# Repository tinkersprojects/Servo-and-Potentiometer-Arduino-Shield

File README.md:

# Servo-and-Potentiometer-Arduino-Shield
[https://tinkersprojects.com/](https://tinkersprojects.com/)

This shield is for the Arduino uno and has 6 potentiometer on every analog pin. The shield can also hold 14 servos (one for every digital pin). There are also 2 buttons on the inturuptet pins 2 and 3. 

Can get the PCB from https://www.tindie.com/products/williambailes/servo-and-potentiometer-arduino-shield/

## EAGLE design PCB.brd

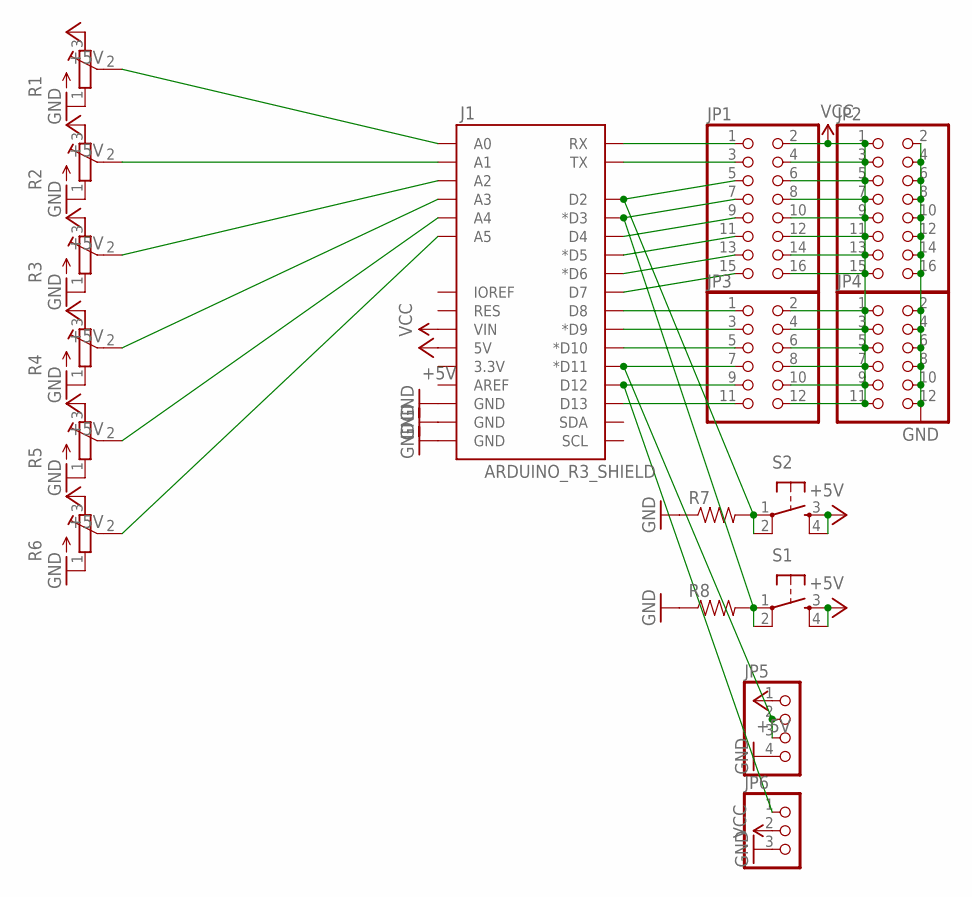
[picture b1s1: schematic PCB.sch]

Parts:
J1: ARDUINO_R3_SHIELD; UNO_R3_SHIELD
JP1, JP2: PINHD-2X8; 2X08
JP3, JP4: PINHD-2X6; 2X06
JP5: PINHD-1X4; 1X04
JP6: PINHD-1X3; 1X03
R1, R2, R3, R4, R5, R6: R-TRIMM3339P; RTRIM3339P
R7, R8: RESISTOREZ; AXIAL-0.3EZ
S1, S2: TAC_SWITCHPTH; TACTILE-PTH

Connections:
+5V: J1.5V, JP5.1, R1.3 (E), R2.3 (E), R3.3 (E), R4.3 (E), R5.3 (E), R6.3 (E), S1.3, S1.4, S2.3, S2.4
GND: J1.GND@0 (GND), J1.GND@1 (GND), J1.GND@2 (GND), JP2.2, JP2.4, JP2.6, JP2.8, JP2.10, JP2.12, JP2.14, JP2.16, JP4.2, JP4.4, JP4.6, JP4.8, JP4.10, JP4.12, JP5.4, JP6.3, R1.1 (A), R2.1 (A), R3.1 (A), R4.1 (A), R5.1 (A), R6.1 (A), R7.P$1 (1), R8.P$1 (1)
unnamed: J1.A5, R6.2 (S)
unnamed: J1.A4, R5.2 (S)
unnamed: J1.A3, R4.2 (S)
unnamed: J1.A2, R3.2 (S)
unnamed: J1.A1, R2.2 (S)
unnamed: J1.A0, R1.2 (S)
unnamed: J1.RX, JP1.1
unnamed: J1.D2, JP1.5, R7.P$2 (2), S2.1, S2.2
unnamed: J1.D3 (*D3), JP1.7, R8.P$2 (2), S1.1, S1.2
unnamed: J1.D4, JP1.9
unnamed: J1.D5 (*D5), JP1.11
unnamed: J1.D6 (*D6), JP1.13
unnamed: J1.D7, JP1.15
unnamed: J1.TX, JP1.3
unnamed: J1.D11 (*D11), JP3.7, JP5.2, JP5.3
unnamed: J1.D8, JP3.1
unnamed: J1.D9 (*D9), JP3.3
unnamed: J1.D10 (*D10), JP3.5
unnamed: J1.D12, JP3.9, JP6.1
unnamed: J1.D13, JP3.11
VCC: J1.VIN, JP1.2, JP1.4, JP1.6, JP1.8, JP1.10, JP1.12, JP1.14, JP1.16, JP2.1, JP2.3, JP2.5, JP2.7, JP2.9, JP2.11, JP2.13, JP2.15, JP3.2, JP3.4, JP3.6, JP3.8, JP3.10, JP3.12, JP4.1, JP4.3, JP4.5, JP4.7, JP4.9, JP4.11, JP6.2

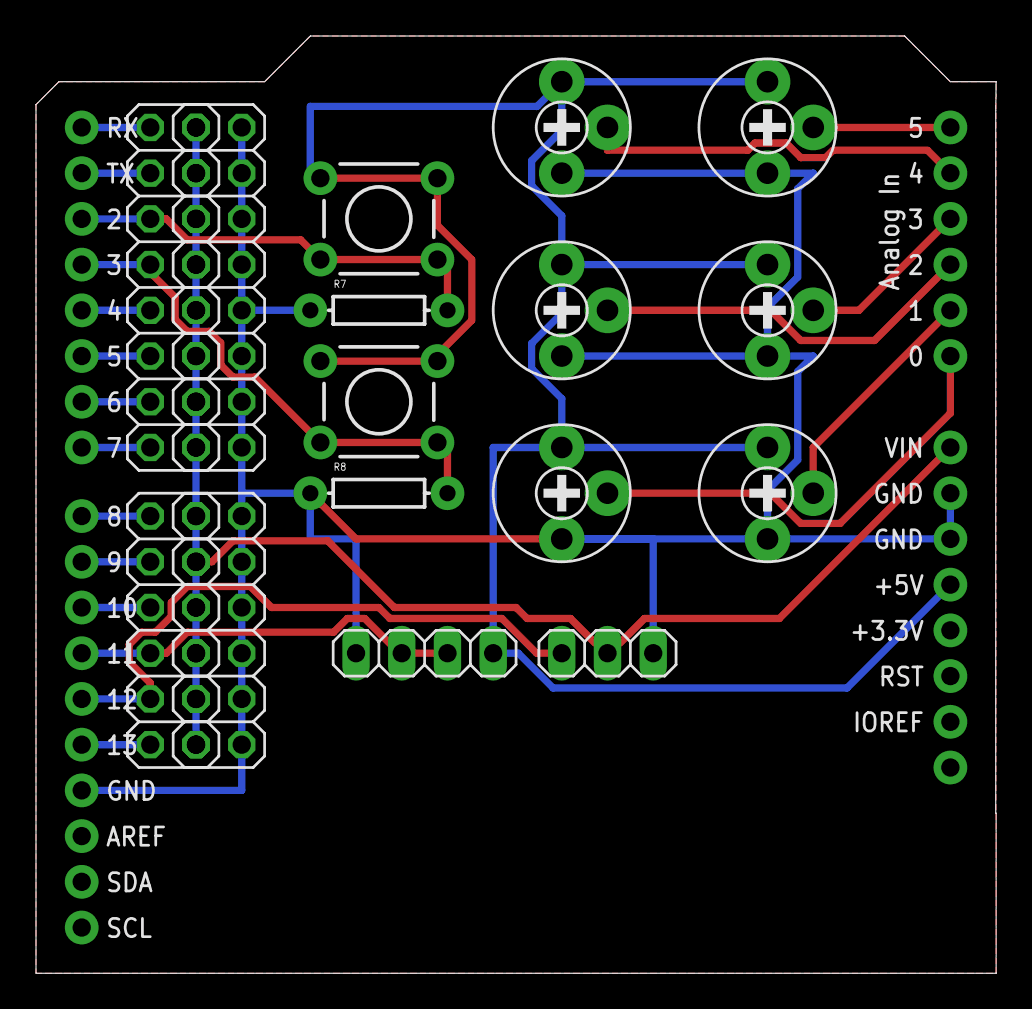
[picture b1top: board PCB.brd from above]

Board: 2 copper layers, 53.3 x 52.1 mm, 17 parts (0 on the bottom side), 23 nets.

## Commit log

2018-04-11 Add files via upload
    Upload PCB files
2018-04-11 Update LICENSE
    update

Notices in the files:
parts and their libraries:
SparkFun-Boards: Licensing: Creative Commons ShareAlike 4.0 International - https://creativecommons.org/licenses/by-sa/4.0
